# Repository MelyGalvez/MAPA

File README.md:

# MAPA
Module d'Apprentissage du Piano Automatisé (MAPA)

# Table des matières
1. Equipe de travail
2. Description du projet
3. Journal de bord

# 1. Equipe de travail

Software: Mely & Marin

Hardware: Justine & Jiajing

# 2. Description du projet
# 3. Journal de bord

## Première session 17 septembre 2024

Mise en place du projet MAPA. Brainstorming sur les différents point du sujet MAPA. Conception du diagramme fonctionnel du projet.

<div align="center">
  
</div>
<div align="center">
Schéma des étapes du projet
</div>

<div align="center">
  
</div>
<div align="center">
Diagramme fonctionnel primitif
</div>

## Deuxième session 24 septembre 2024
Software: début de recherche de code pour traiter un fichier MIDI grâce à la STM32. Aussi recherche de code pour traiter un fichier audio (.wav)

Hardware: recherche des références des composants
## Troisième session 01 octobre 2024
Software: Avancement et réglage des erreurs du code de la semaine dernière

Hardware: Listes des références presque fini pour commander. Emprunt d'une petite bande LED à Mme.Kittel pour tester un code

## Quatrième session 8 octobre 2024

Présentation de l'avancement du projet

Software: Tuto en cours de compréhension, bibliothèque CMSIS installé. Code de control de Led avancé

Hardware: phase final des listes de références, régulateur, ruban led. Classification des composants dans des excels différent selon les contructeur pour commander

## Cinquième session 22 octobre 2024

## Sixième session 05 novembre 2024
Chez pas
## Septième session 12 novembre 2024

Code pour l'initialisation du ruban led avec 3 boutons

## Huitième session 19 novembre 2024

Mesure des touches du piano pour connaitre le ruban led ou  matrice de led à prendre

## Neuvième session 26 novembre 2024

Décision finale pour le choix de ruban led 

## Dixième session 03 décembre 2024
Mise en forme

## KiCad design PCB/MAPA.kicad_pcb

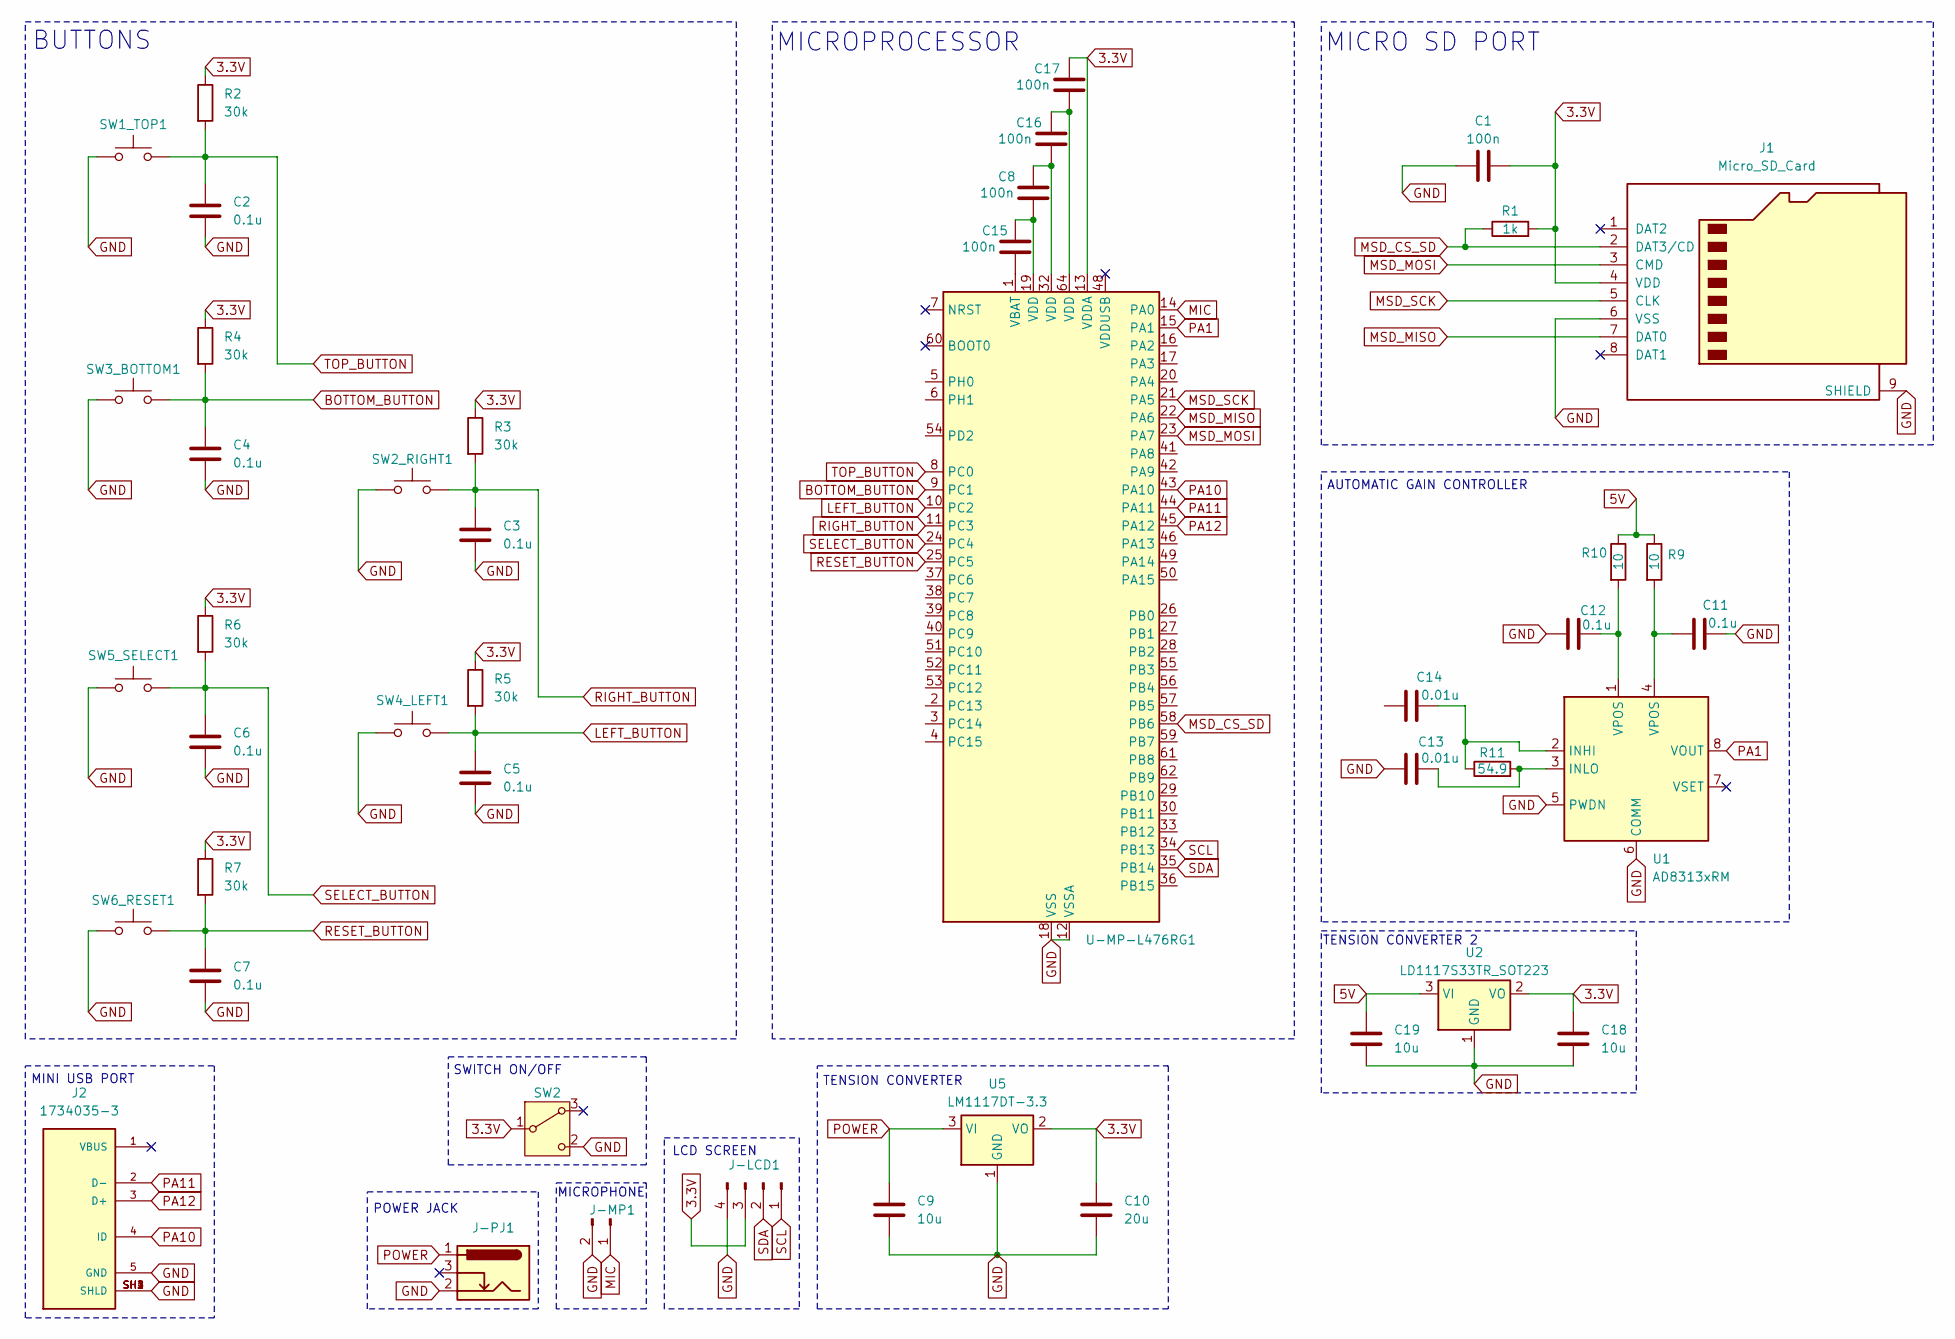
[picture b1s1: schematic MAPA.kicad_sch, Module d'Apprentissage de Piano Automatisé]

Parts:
C1, C8, C15, C16, C17: 100n; C_0603_1608Metric
C2, C3, C4, C5, C6, C7, C11, C12: 0.1u; C_0603_1608Metric
C9, C18, C19: 10u; C_0603_1608Metric
C10: 20u; C_0603_1608Metric
C13, C14: 0.01u; C_0603_1608Metric
J1: Micro_SD_Card; microSD_HC_Molex_47219-2001
J2: 1734035-3; TE_1734035-3; PARTREV F
J-LCD1: Conn_01x04_Pin; PinHeader_1x04_P2.54mm_Horizontal
J-MP1: Conn_01x02_Pin; PinHeader_1x02_P2.54mm_Horizontal
J-PJ1: Barrel_Jack_Switch; BarrelJack_Horizontal
R1: 1k; R_0201_0603Metric
R2, R3, R4, R5, R6, R7: 30k; R_0201_0603Metric
R9, R10: 10; R_0201_0603Metric
R11: 54.9; R_0201_0603Metric
SW1_TOP1, SW2_RIGHT1, SW3_BOTTOM1, SW4_LEFT1, SW5_SELECT1, SW6_RESET1: SW_Push; SW_PUSH_6mm
SW2: SW_Wuerth_450301014042; SW_Slide-03_Wuerth-WS-SLTV_10x2.5x6.4_P2.54mm
U1: AD8313xRM; MSOP-8_3x3mm_P0.65mm
U2: LD1117S33TR_SOT223; SOT-223-3_TabPin2
U5: LM1117DT-3.3; TO-252-3_TabPin2
U-MP-L476RG1: STM32L476RGTx; LQFP-64_10x10mm_P0.5mm

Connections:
3.3V: C1.2, C10.1, C17.1, C18.1, J1.4 (VDD), J-LCD1.3, R1.2, R2.1, R3.1, R4.1, R5.1, R6.1, R7.1, SW2.1 (B), U2.2 (VO), U5.2 (VO), U-MP-L476RG1.13 (VDDA)
5V: C19.1, R9.1, R10.1, U2.3 (VI)
BOTTOM_BUTTON: C4.1, R4.2, SW3_BOTTOM1.2, U-MP-L476RG1.9 (PC1)
GND: C1.1, C2.2, C3.2, C4.2, C5.2, C6.2, C7.2, C9.2, C10.2, C11.2, C12.1, C13.1, C18.2, C19.2, J1.6 (VSS), J1.9 (SHIELD), J2.5 (GND), J2.SH1 (SHLD), J2.SH2 (SHLD), J2.SH3 (SHLD), J2.SH4 (SHLD), J-LCD1.4, J-MP1.2, J-PJ1.2, SW1_TOP1.1, SW2.2 (C), SW2_RIGHT1.1, SW3_BOTTOM1.1, SW4_LEFT1.1, SW5_SELECT1.1, SW6_RESET1.1, U1.5 (PWDN), U1.6 (COMM), U2.1 (GND), U5.1 (GND), U-MP-L476RG1.12 (VSSA), U-MP-L476RG1.18 (VSS), U-MP-L476RG1.31 (VSS), U-MP-L476RG1.47 (VSS), U-MP-L476RG1.63 (VSS)
LEFT_BUTTON: C5.1, R5.2, SW4_LEFT1.2, U-MP-L476RG1.10 (PC2)
MIC: J-MP1.1, U-MP-L476RG1.14 (PA0)
MSD_CS_SD: J1.2 (DAT3/CD), R1.1, U-MP-L476RG1.58 (PB6)
MSD_MISO: J1.7 (DAT0), U-MP-L476RG1.22 (PA6)
MSD_MOSI: J1.3 (CMD), U-MP-L476RG1.23 (PA7)
MSD_SCK: J1.5 (CLK), U-MP-L476RG1.21 (PA5)
unnamed: C11.1, R9.2, U1.4 (VPOS)
unnamed: C12.2, R10.2, U1.1 (VPOS)
unnamed: C8.2, C15.1, U-MP-L476RG1.19 (VDD)
unnamed: C16.1, C17.2, U-MP-L476RG1.64 (VDD)
unnamed: C8.1, C16.2, U-MP-L476RG1.32 (VDD)
unnamed: C14.2, R11.1, U1.2 (INHI)
unnamed: C13.2, R11.2, U1.3 (INLO)
unnamed: C15.2, U-MP-L476RG1.1 (VBAT)
PA1: U1.8 (VOUT), U-MP-L476RG1.15 (PA1)
PA10: J2.4 (ID), U-MP-L476RG1.43 (PA10)
PA11: J2.2 (D-), U-MP-L476RG1.44 (PA11)
PA12: J2.3 (D+), U-MP-L476RG1.45 (PA12)
POWER: C9.1, J-PJ1.1, U5.3 (VI)
RESET_BUTTON: C7.1, R7.2, SW6_RESET1.2, U-MP-L476RG1.25 (PC5)
RIGHT_BUTTON: C3.1, R3.2, SW2_RIGHT1.2, U-MP-L476RG1.11 (PC3)
SCL: J-LCD1.1, U-MP-L476RG1.34 (PB13)
SDA: J-LCD1.2, U-MP-L476RG1.35 (PB14)
SELECT_BUTTON: C6.1, R6.2, SW5_SELECT1.2, U-MP-L476RG1.24 (PC4)
TOP_BUTTON: C2.1, R2.2, SW1_TOP1.2, U-MP-L476RG1.8 (PC0)

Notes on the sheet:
TENSION CONVERTER 2
MICROPROCESSOR
SWITCH ON/OFF
LCD SCREEN
MINI USB PORT
TENSION CONVERTER
BUTTONS
MICROPHONE
AUTOMATIC GAIN CONTROLLER
POWER JACK
MICRO SD PORT

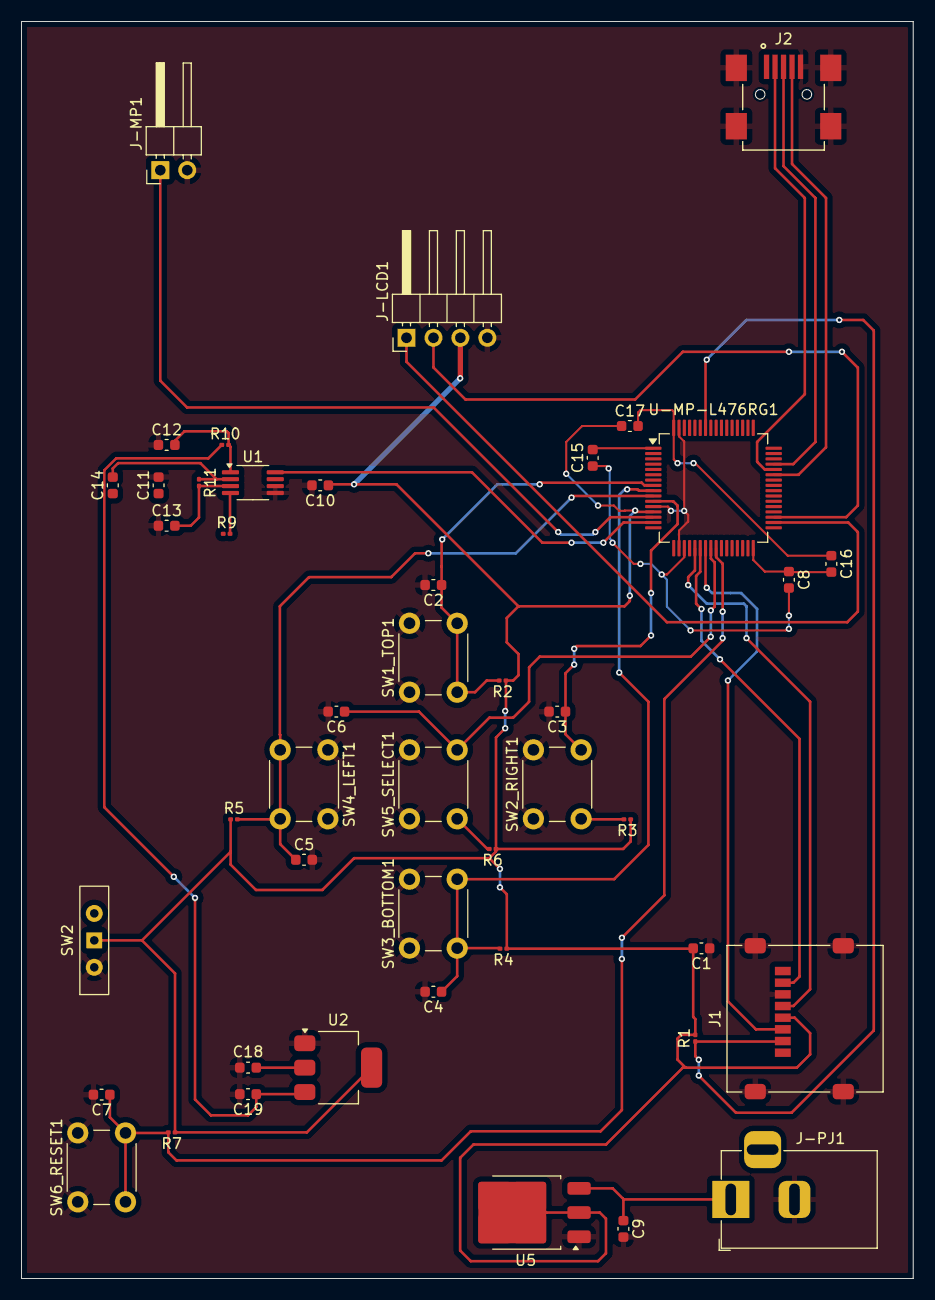
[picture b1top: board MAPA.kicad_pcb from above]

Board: 2 copper layers, 84.1 x 118.5 mm, 45 parts (0 on the bottom side), 29 nets.

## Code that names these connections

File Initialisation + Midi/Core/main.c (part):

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  GPIO_InitStruct.Pull = GPIO_PULLUP;
  HAL_GPIO_Init(GPIOC, &GPIO_InitStruct);

  /*Configure GPIO pins : PC0 PC1 PC2 PC3
                           PC4 PC5 */
  GPIO_InitStruct.Pin = GPIO_PIN_0|GPIO_PIN_1|GPIO_PIN_2|GPIO_PIN_3
                          |GPIO_PIN_4|GPIO_PIN_5;
  GPIO_InitStruct.Mode = GPIO_MODE_IT_RISING;
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  GPIO_InitStruct.Speed = GPIO_SPEED_FREQ_LOW;
  HAL_GPIO_Init(LD2_GPIO_Port, &GPIO_InitStruct);

  /*Configure GPIO pins : PA9 PA10 */
  GPIO_InitStruct.Pin = GPIO_PIN_9|GPIO_PIN_10;
  GPIO_InitStruct.Mode = GPIO_MODE_IT_FALLING;
  GPIO_InitStruct.Pull = GPIO_PULLUP;
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
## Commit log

2024-09-17 Create Fichier
2024-09-17 Create ABC
2024-10-01 Create Composants
2024-10-01 Update Composants
2024-10-01 Update README.md
    ajout dans #1 et dans tableau de bord
2024-12-03 Add files via upload
    Schéma explicatif de l'initialisation de mapa
2024-12-03 Add files via upload
    schéma sur le fonctionnement de l'initialisation de MAPA
2024-12-03 Create abs
2024-12-03 Update and rename main.c to main.c du code pour selectionner les led
2024-12-03 Create Fonctionnal Diagram
2024-12-08 Rename Capture d'écran 2024-12-08 111644.png to LED_data.pnj
2024-12-08 Rename LED_data.pnj to LED_data.png
2025-04-01 Create acs

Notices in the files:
Initialisation + Midi/Core/main.c:
Copyright (c) 2024 STMicroelectronics.
All rights reserved.
This software is licensed under terms that can be found in the LICENSE file
